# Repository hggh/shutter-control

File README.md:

# shutter-control + light control

3x Rolladensteuerung 3x Lichtsteuerung

## parts

  * Varistor S14K275 (Conrad: 500675)
  * fuse holder 5 x 20 mm 6.3 A 250 V/AC ESKA 503.500 (Conrad: 533866

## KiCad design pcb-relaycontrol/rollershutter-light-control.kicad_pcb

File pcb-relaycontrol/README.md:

```
/*
 * Bit 0 = Light 3
 * Bit 1 = Light 2
 * Bit 2 = Light 1
 * Bit 3 = R1 an/aus
 * Bit 4 = R1 runter/hoch
 * Bit 5 = R2 an/aus
 * Bit 6 = R2 runter/hoch
 * Bit 7 = R3 an/aus
 * Bit 8 = R3 runter/hoch
 */
```

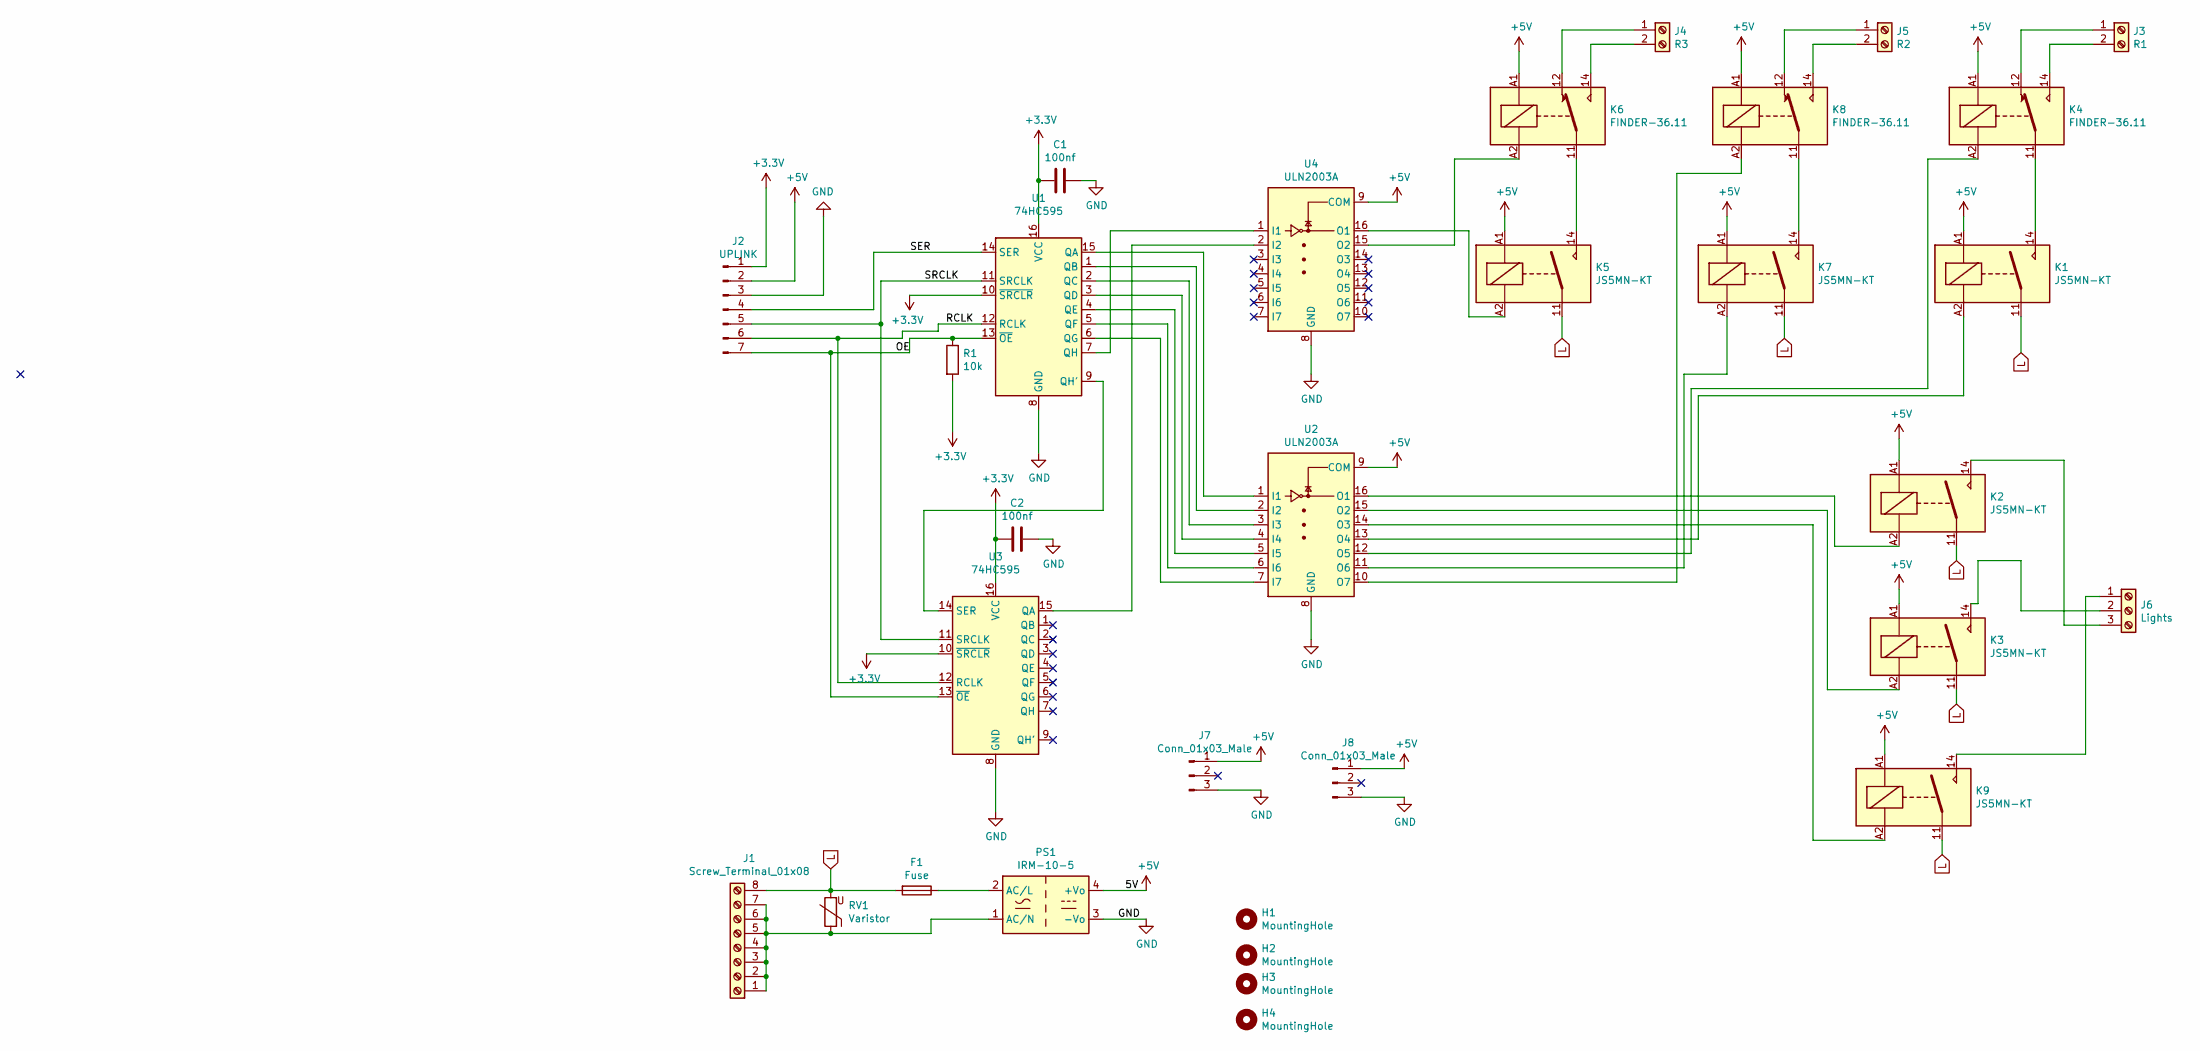
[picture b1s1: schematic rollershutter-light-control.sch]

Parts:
C1, C2: 100nf; C_0805_2012Metric
F1: Fuse; Fuseholder_Cylinder-5x20mm_Schurter_0031_8201_Horizontal_Op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
H1, H2, H3, H4: MountingHole; MountingHole_3.2mm_M3
J1: Screw_Terminal_01x08; RND_Schraubklemme_8pol
J2: UPLINK; PinHeader_1x07_P2.54mm_Vertical
J3: R1; RND_Schraubklemme_2pol
J4: R3; RND_Schraubklemme_2pol
J5: R2; RND_Schraubklemme_2pol
J6: Lights; RND_Schraubklemme_3pol
J7, J8: Conn_01x03_Male; PinHeader_1x03_P2.54mm_Horizontal
K1, K2, K3, K5, K7, K9: JS5MN-KT; js5mn-kt
K4, K6, K8: FINDER-36.11; Finder 36.11.9
PS1: IRM-10-5; Converter_ACDC_MeanWell_IRM-10-xx_THT
R1: 10k; R_0805_2012Metric
RV1: Varistor; RV_Disc_D12mm_W3.9mm_P7.5mm
U1, U3: 74HC595; SOIC-16_3.9x9.9mm_P1.27mm
U2, U4: ULN2003A; SOIC-16_3.9x9.9mm_P1.27mm

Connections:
+3V3: C1.2, C2.2, J2.1, R1.2, U1.10 (~SRCLR), U1.16 (VCC), U3.10 (~SRCLR), U3.16 (VCC)
+5V: J2.2, J7.1, J8.1, K1.A1, K2.A1, K3.A1, K4.A1, K5.A1, K6.A1, K7.A1, K8.A1, K9.A1, PS1.4 (+Vo), U2.9 (COM), U4.9 (COM)
/OE: J2.7, R1.1, U1.13 (~OE), U3.13 (~OE)
/RCLK: J2.6, U1.12 (RCLK), U3.12 (RCLK)
/SER: J2.4, U1.14 (SER)
/SRCLK: J2.5, U1.11 (SRCLK), U3.11 (SRCLK)
GND: C1.1, C2.1, J2.3, J7.3, J8.3, PS1.3 (-Vo), U1.8 (GND), U2.8 (GND), U3.8 (GND), U4.8 (GND)
L: F1.2, J1.8, K1.11, K2.11, K3.11, K5.11, K7.11, K9.11, RV1.2
unnamed: F1.1, PS1.2 (AC/L)
unnamed: J1.1, J1.2, J1.3, J1.4, J1.5, J1.6, J1.7, PS1.1 (AC/N), RV1.1
unnamed: J3.1, K4.12
unnamed: J3.2, K4.14
unnamed: J4.1, K6.12
unnamed: J4.2, K6.14
unnamed: J5.1, K8.12
unnamed: J5.2, K8.14
unnamed: J6.1, K9.14
unnamed: J6.2, K3.14
unnamed: J6.3, K2.14
unnamed: K1.14, K4.11
unnamed: K1.A2, U2.13 (O4)
unnamed: K2.A2, U2.16 (O1)
unnamed: K3.A2, U2.15 (O2)
unnamed: K4.A2, U2.12 (O5)
unnamed: K5.14, K6.11
unnamed: K5.A2, U4.16 (O1)
unnamed: K6.A2, U4.15 (O2)
unnamed: K7.14, K8.11
unnamed: K7.A2, U2.11 (O6)
unnamed: K8.A2, U2.10 (O7)
unnamed: K9.A2, U2.14 (O3)
unnamed: U1.1 (QB), U2.2 (I2)
unnamed: U1.2 (QC), U2.3 (I3)
unnamed: U1.3 (QD), U2.4 (I4)
unnamed: U1.4 (QE), U2.5 (I5)
unnamed: U1.5 (QF), U2.6 (I6)
unnamed: U1.6 (QG), U2.7 (I7)
unnamed: U1.7 (QH), U4.1 (I1)
unnamed: U1.9 (QH'), U3.14 (SER)
unnamed: U1.15 (QA), U2.1 (I1)
unnamed: U3.15 (QA), U4.2 (I2)

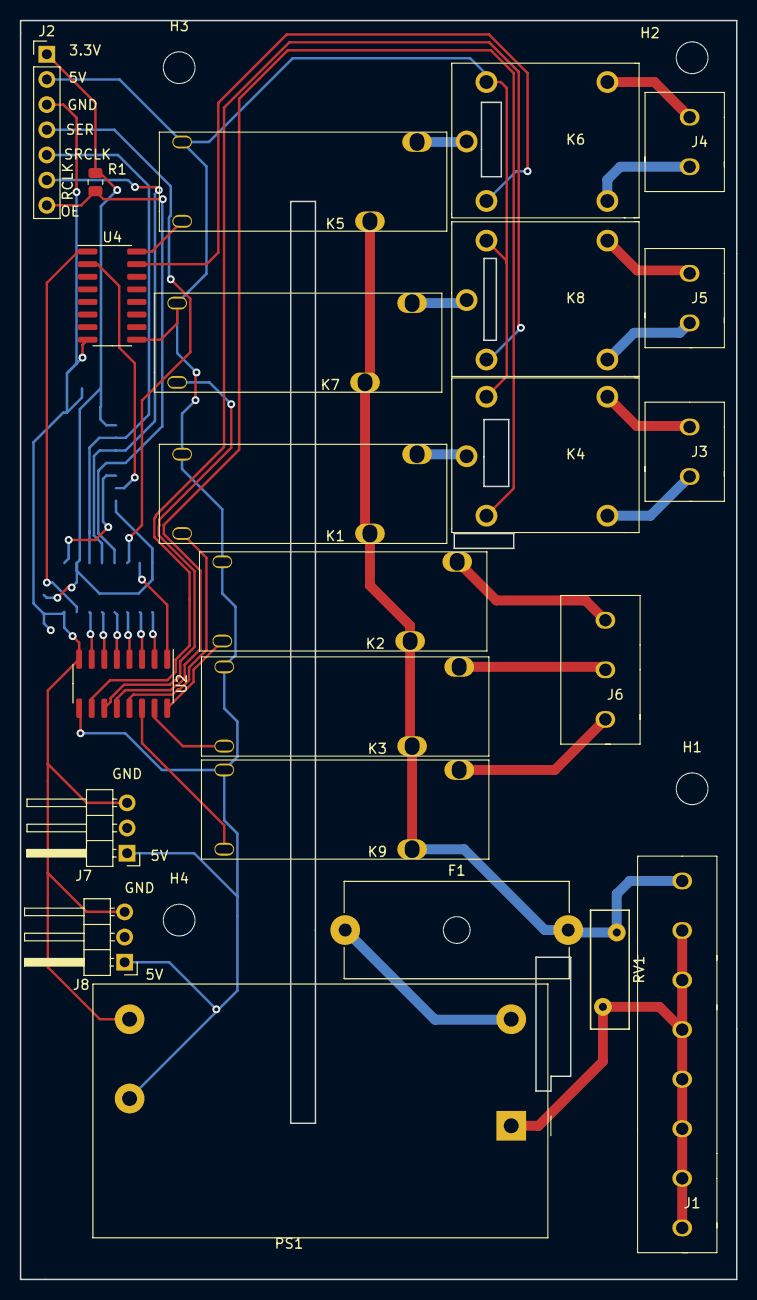
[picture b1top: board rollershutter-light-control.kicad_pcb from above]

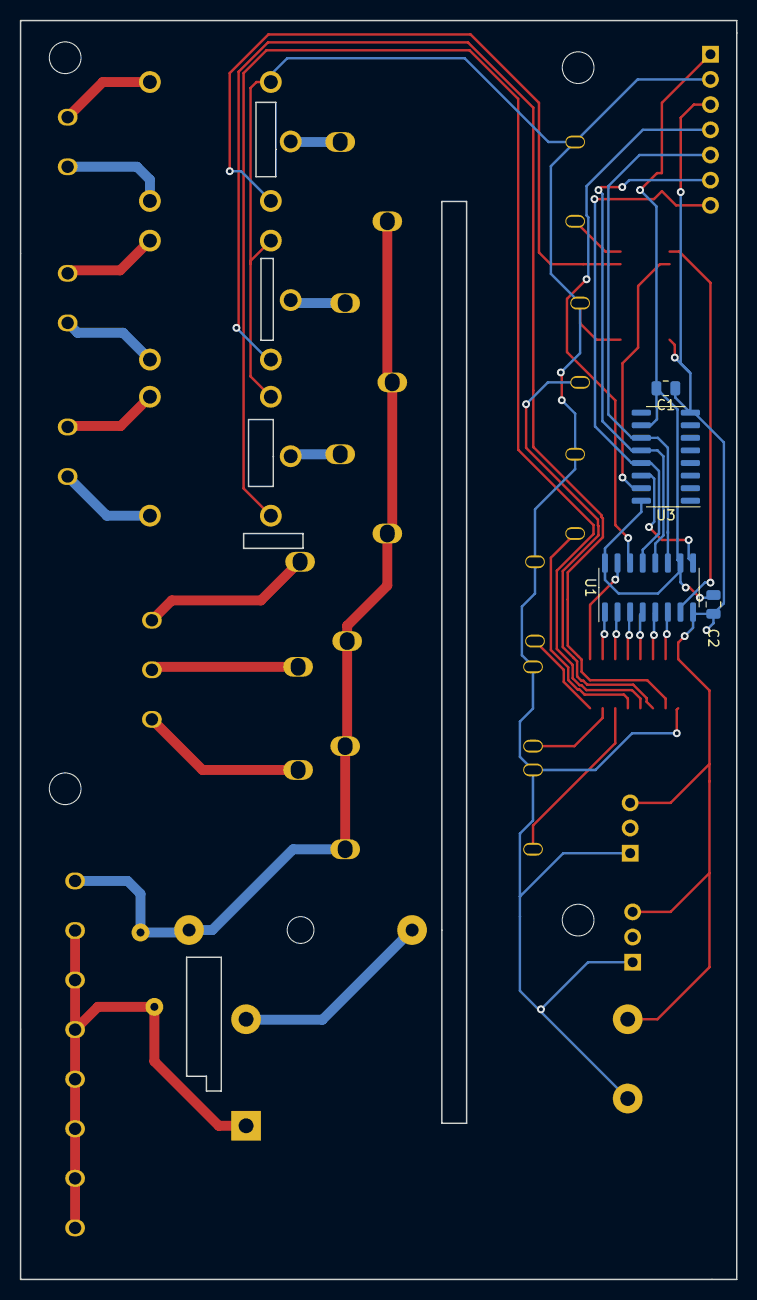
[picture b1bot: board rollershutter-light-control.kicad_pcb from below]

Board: 2 copper layers, 72.2 x 127.0 mm, 31 parts (4 on the bottom side), 41 nets.

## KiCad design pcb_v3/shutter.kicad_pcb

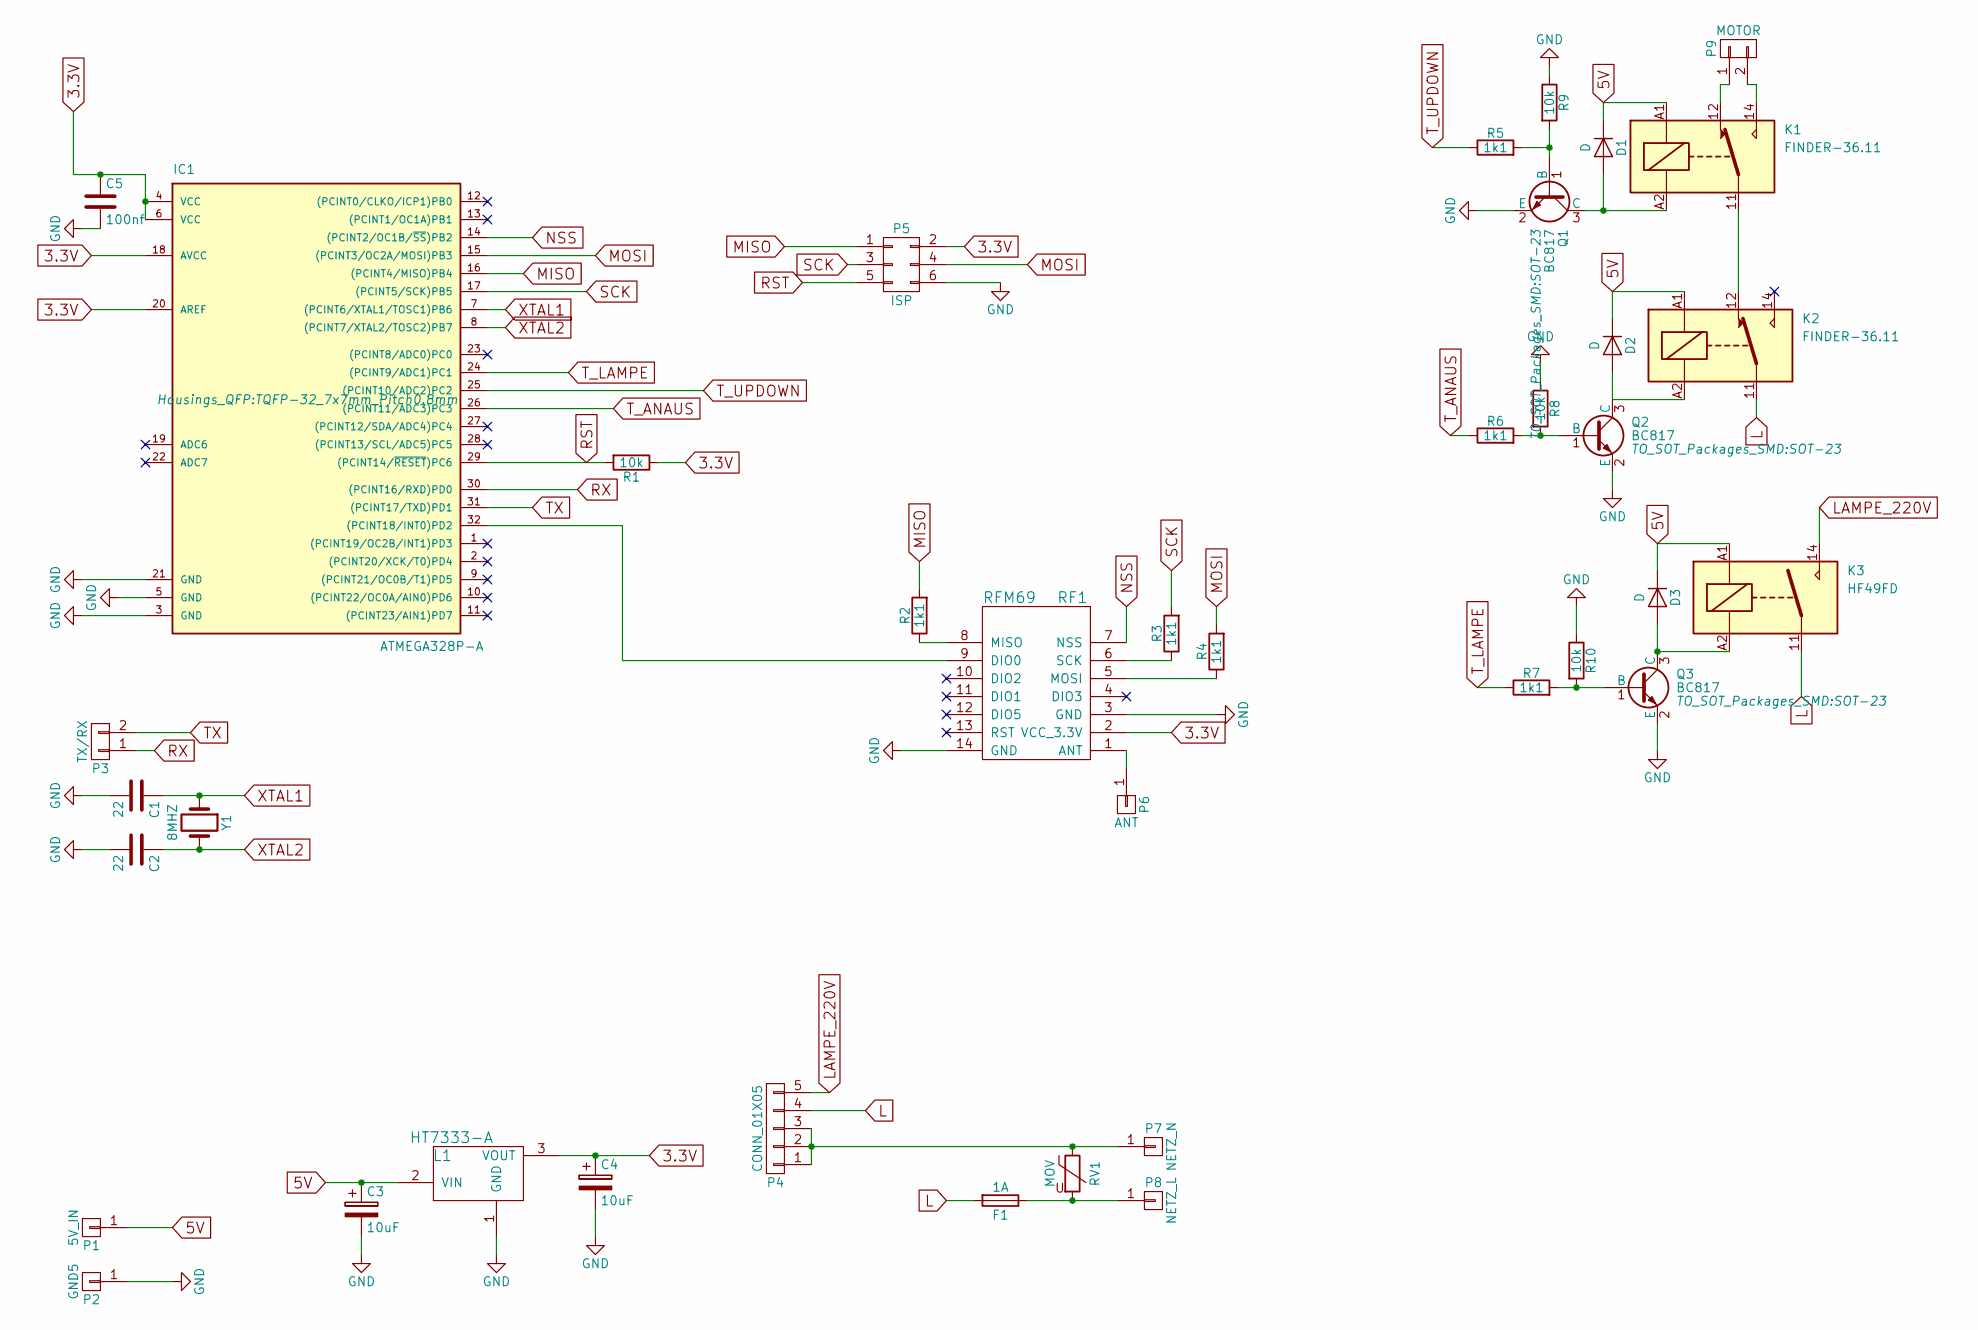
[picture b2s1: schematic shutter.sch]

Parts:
C1, C2: 22; C_0805_HandSoldering
C3, C4: 10uF; c_elec_5x5.8
C5: 100nf; C_0805_HandSoldering
D1, D2, D3: D; MELF_Handsoldering
F1: 1A; Fuseholder5x20_horiz_SemiClosed_Casing10x25mm
IC1: ATMEGA328P-A; TQFP-32_7x7mm_Pitch0.8mm
K1, K2: FINDER-36.11; Finder 36.11.9
K3: HF49FD
L1: HT7333-A; SOT89-3_Housing_Handsoldering
P1: 5V_IN; SolderWirePad_single_1mmDrill
P2: GND5; SolderWirePad_single_1mmDrill
P3: TX/RX; Pin_Header_Straight_1x02
P4: CONN_01X05; RND_Schraubklemme_5pol
P5: ISP; isp
P6: ANT; SolderWirePad_single_1mmDrill
P7: NETZ_N; SolderWirePad_single_2mmDrill
P8: NETZ_L; SolderWirePad_single_2mmDrill
P9: MOTOR; RND_Schraubklemme_2pol
Q1, Q2, Q3: BC817; SOT-23
R1, R8, R9, R10: 10k; R_0805_HandSoldering
R2, R3, R4, R5, R6, R7: 1k1; R_0805_HandSoldering
RF1: RFM69; RFM96
RV1: MOV; RV_Disc_D12_W3.9_P7.5
Y1: 8MHZ; Crystal_HC49-SD_SMD

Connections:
5V: C3.1, D1.1 (K), D2.1 (K), D3.1 (K), K1.A1, K2.A1, K3.A1, L1.2 (VIN), P1.1
GND: C1.2, C2.2, C3.2, C4.2, C5.2, IC1.3 (GND), IC1.5 (GND), IC1.21 (GND), L1.1 (GND), P2.1, P5.6, Q1.2 (E), Q2.2 (E), Q3.2 (E), R8.1, R9.1, R10.1, RF1.3 (GND), RF1.14 (GND)
L: F1.2, K2.11, K3.11, P4.4
LAMPE_220V: K3.14, P4.5
MISO: IC1.16 ((PCINT4/MISO)PB4), P5.1, R2.2
MOSI: IC1.15 ((PCINT3/OC2A/MOSI)PB3), P5.4, R4.2
NSS: IC1.14 ((PCINT2/OC1B/~SS~)PB2), RF1.7 (NSS)
unnamed: D1.2 (A), K1.A2, Q1.3 (C)
unnamed: D2.2 (A), K2.A2, Q2.3 (C)
unnamed: D3.2 (A), K3.A2, Q3.3 (C)
unnamed: F1.1, P8.1, RV1.2
unnamed: IC1.32 ((PCINT18/INT0)PD2), RF1.9 (DIO0)
unnamed: K1.11, K2.12
unnamed: K1.12, P9.1
unnamed: K1.14, P9.2
unnamed: P4.1, P4.2, P4.3, P7.1, RV1.1
unnamed: P6.1, RF1.1 (ANT)
unnamed: Q1.1 (B), R5.2, R9.2
unnamed: Q2.1 (B), R6.2, R8.2
unnamed: Q3.1 (B), R7.2, R10.2
unnamed: R2.1, RF1.8 (MISO)
unnamed: R3.1, RF1.6 (SCK)
unnamed: R4.1, RF1.5 (MOSI)
RST: IC1.29 ((PCINT14/~RESET~)PC6), P5.5, R1.2
RX: IC1.30 ((PCINT16/RXD)PD0), P3.1
SCK: IC1.17 ((PCINT5/SCK)PB5), P5.3, R3.2
TX: IC1.31 ((PCINT17/TXD)PD1), P3.2
T_ANAUS: IC1.26 ((PCINT11/ADC3)PC3), R6.1
T_LAMPE: IC1.24 ((PCINT9/ADC1)PC1), R7.1
T_UPDOWN: IC1.25 ((PCINT10/ADC2)PC2), R5.1
XTAL1: C1.1, IC1.7 ((PCINT6/XTAL1/TOSC1)PB6), Y1.1
XTAL2: C2.1, IC1.8 ((PCINT7/XTAL2/TOSC2)PB7), Y1.2

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
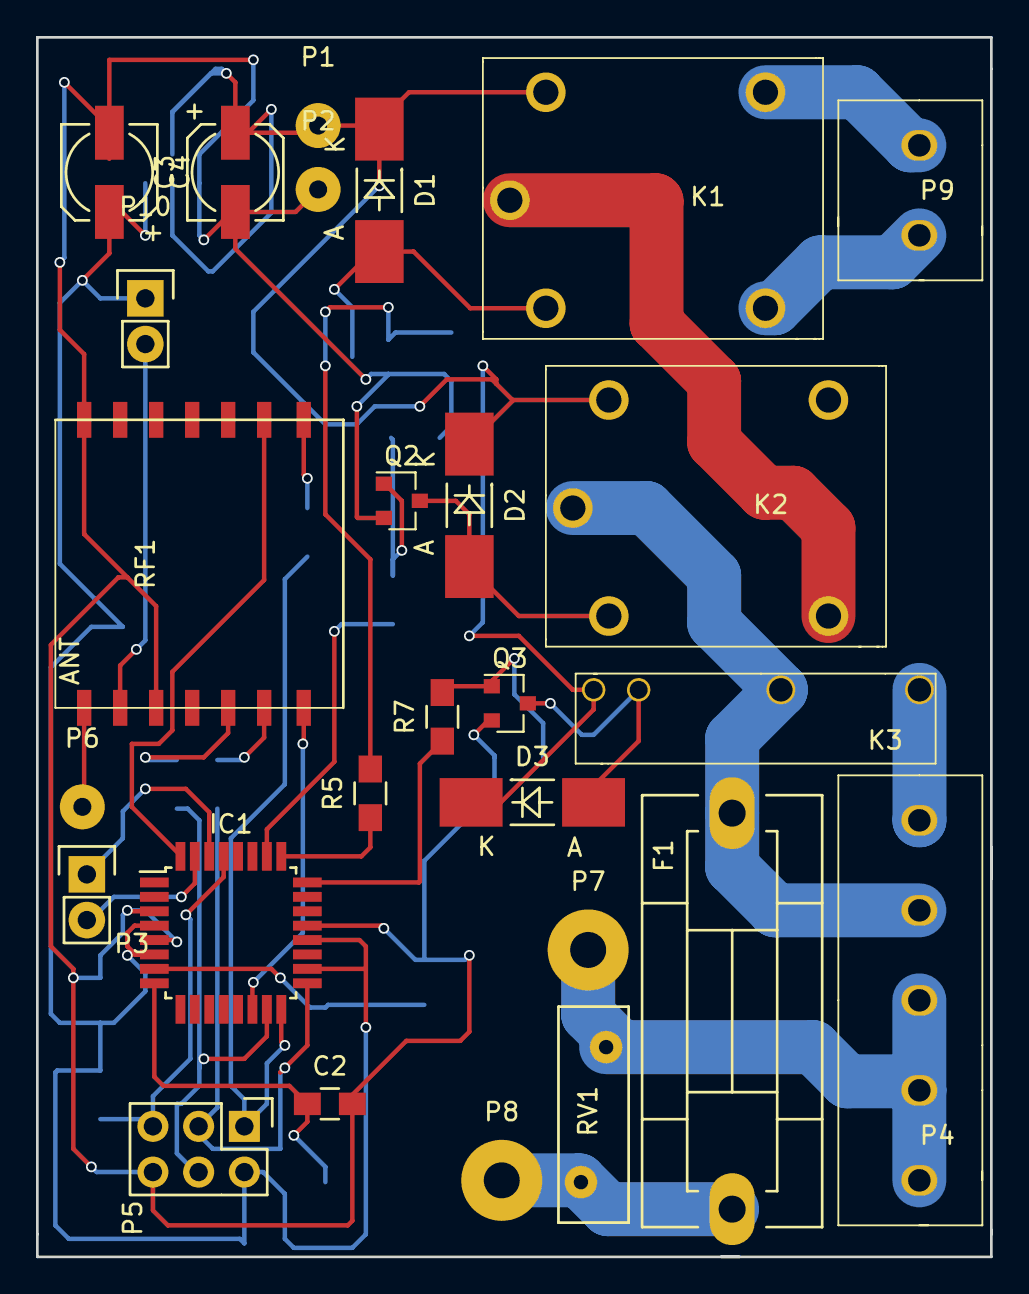
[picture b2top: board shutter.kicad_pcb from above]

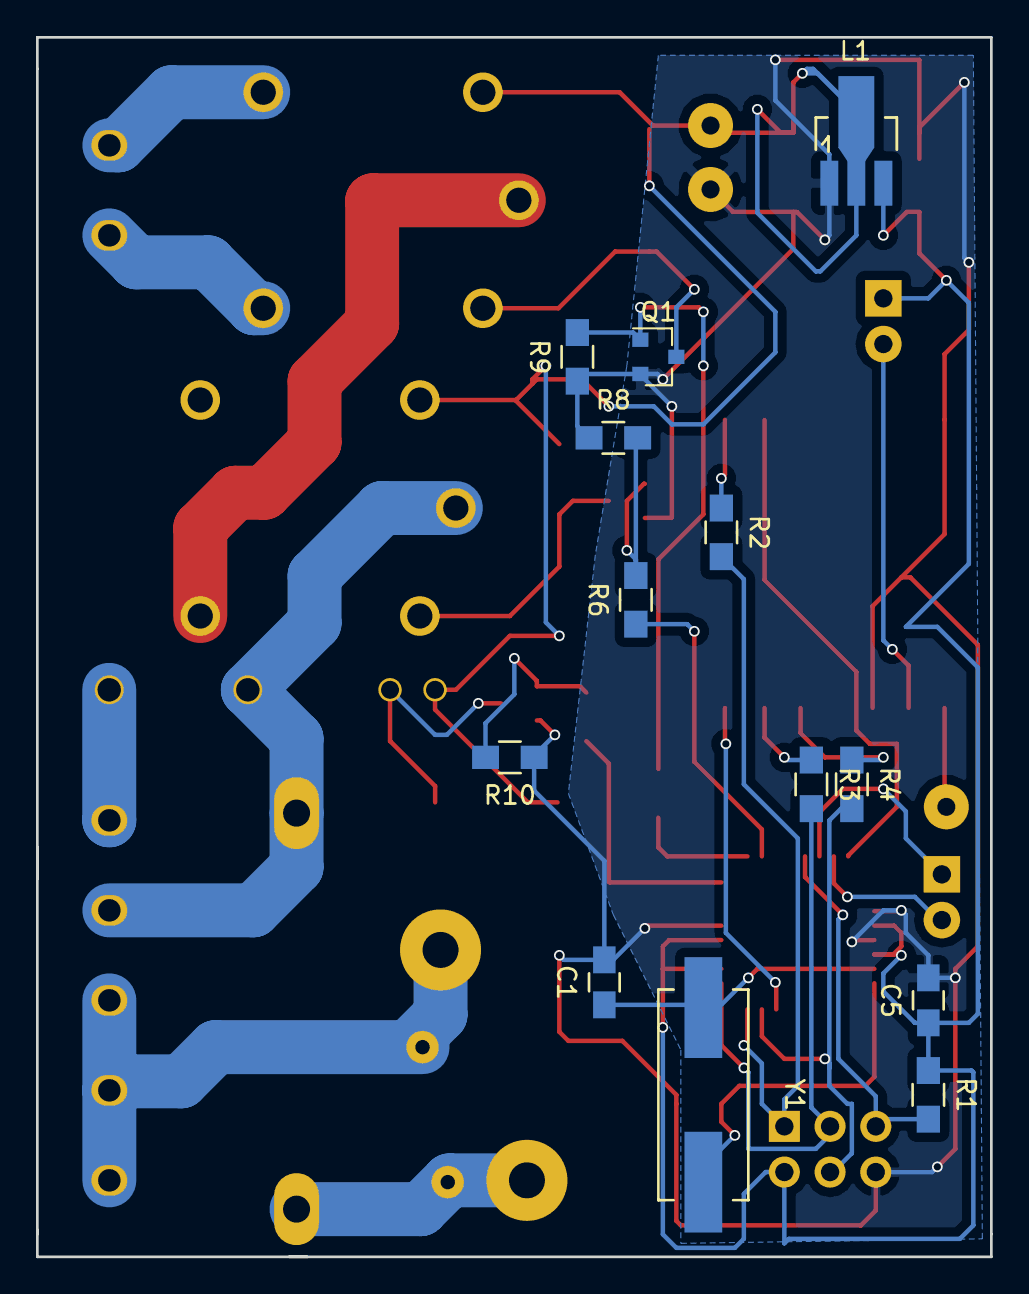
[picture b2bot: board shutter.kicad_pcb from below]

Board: 2 copper layers, 53.0 x 67.8 mm, 40 parts (13 on the bottom side), 34 nets.

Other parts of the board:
P10: ON/OFF; Pin_Header_Straight_1x02

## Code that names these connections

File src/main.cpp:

#include "Arduino.h"
#include <ESP8266WiFi.h>
#include <ArduinoOTA.h>

#include <PubSubClient.h>

#include <ShiftOutRegister.h>
#include <Shutter.h>
#include <Light.h>
#include "config.h"

extern "C" {
#include "user_interface.h"
}

WiFiClient espClient;
PubSubClient client(espClient);
WiFiServer server(80);

ShiftOutRegister sh_register;
Shutter shutter1;
Shutter shutter2;
Light light1;
Light light2;

os_timer_t Timer1;


void timerCall(void*z) {
  shutter1.timer();
  shutter2.timer();
}

void setup_timer1(void) {
  os_timer_setfn(&Timer1, timerCall, NULL);
  os_timer_arm(&Timer1, 1000, true);
}

void mqtt_check_connection() {
  if (!client.connected()) {
    client.connect("roller-light-sun-blind-windspeed", MQTT_USERNAME, MQTT_PASSWORD);
  }
}

void wificonnect() {
  WiFi.mode(WIFI_STA);
  WiFi.begin(SECRET_SSID, SECRET_PASS);
  while (WiFi.status() != WL_CONNECTED) {
    delay(200);
  }
  mqtt_check_connection();
}

void setup() {
  WiFi.hostname("roller-light-sun-blind-windspeed");

  client.setServer(MQTT_SERVER, 1883);

  setup_timer1();
  wificonnect();

  server.begin();

  /**
     D6/GPIO12 == data/SER
     D2/GPIO4  == shift/SRCLK
     D1/GPIO5  == store/RCLK
     D5/GPIO14  == enable/OE
  **/
  sh_register.init(D6, D2, D1, D5, 8);

  shutter1.begin(2, 3, 40, &sh_register);
  shutter2.begin(4, 5, 60, &sh_register);

  light1.begin(0, &sh_register);
  light2.begin(1, &sh_register);

  ArduinoOTA.setPassword(OTA_PASS);
  ArduinoOTA.begin();
}

void loop() {
  delay(1);
  if (WiFi.status() != WL_CONNECTED) {
    wificonnect();
  }

  ArduinoOTA.handle();
  mqtt_check_connection();
  client.loop();

  // Check if a client has connected
  WiFiClient client = server.available();
  if (!client) {
    return;
  }

  // Wait until the client sends some data
  while (!client.available()) {
    delay(1);
  }

  // Read the first line of the request
  String header_line = client.readStringUntil('\r');
  client.flush();

  // Light 1
  if (header_line.startsWith("GET /light1/on")) {
    light1.on();
  }
  if (header_line.startsWith("GET /light1/off")) {
    light1.off();
  }

  // Light 2
  if (header_line.startsWith("GET /light2/on")) {
    light2.on();
  }
  if (header_line.startsWith("GET /light2/off")) {
    light2.off();
  }


  // Shutter1
  if (header_line.startsWith("GET /shutter1/down")) {
    shutter1.down();
  }
  if (header_line.startsWith("GET /shutter1/up")) {
    shutter1.up();
  }
  if (header_line.startsWith("GET /shutter1/halt")) {
    shutter1.halt();
  }

  // Shutter2
  if (header_line.startsWith("GET /shutter2/down")) {
    shutter2.down();
  }
  if (header_line.startsWith("GET /shutter2/up")) {
    shutter2.up();
  }
  if (header_line.startsWith("GET /shutter2/halt")) {
    shutter2.halt();
  }

  String s = "HTTP/1.1 200 OK\r\nContent-Type: text/plain\r\n\r\nOK";
  client.print(s);
  delay(1);
}

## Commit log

2017-09-30 added gitignore
2017-09-30 added code
2017-09-30 better operation for motor safety
2017-09-30 added status command with RFM69 temperature call
2017-09-30 control mgmt programm
2017-10-25 switched to #ifdef
2017-10-25 removed external library sleep myself
2018-01-20 put rfm69 back into rx mode
2018-02-17 added v3 of pcb
2018-02-17 added new Pcb
2018-02-17 updated pcb
2018-02-18 added jumper for power rfm69
2018-02-22 updated pcb, filled zones
2018-03-02 added light relais
2018-05-13 updated schema
2018-05-13 disable adc to save power
2018-09-16 changed to platform IO
2018-09-16 removed swp
2018-09-16 updated gitignore swp
2018-09-16 changed to jeetlib for sleeping
2018-09-16 removed senderid
2018-11-02 added Light/Shutter class
2018-11-02 remove default value
2018-11-02 use wifi101 with WINC1500
2018-11-02 move to pio lib directory
2018-11-09 move while
2018-11-25 update to NodeMCU
2018-11-25 removed serial print
2019-04-12 new pins, removed shutter3
2019-04-12 changed to new libraries
2020-02-02 add pcb holder
2020-02-02 new holder for wind sensor
2021-04-23 removed old
2021-04-23 update hostname
2021-06-06 add PCB
2021-06-07 removed outdated
